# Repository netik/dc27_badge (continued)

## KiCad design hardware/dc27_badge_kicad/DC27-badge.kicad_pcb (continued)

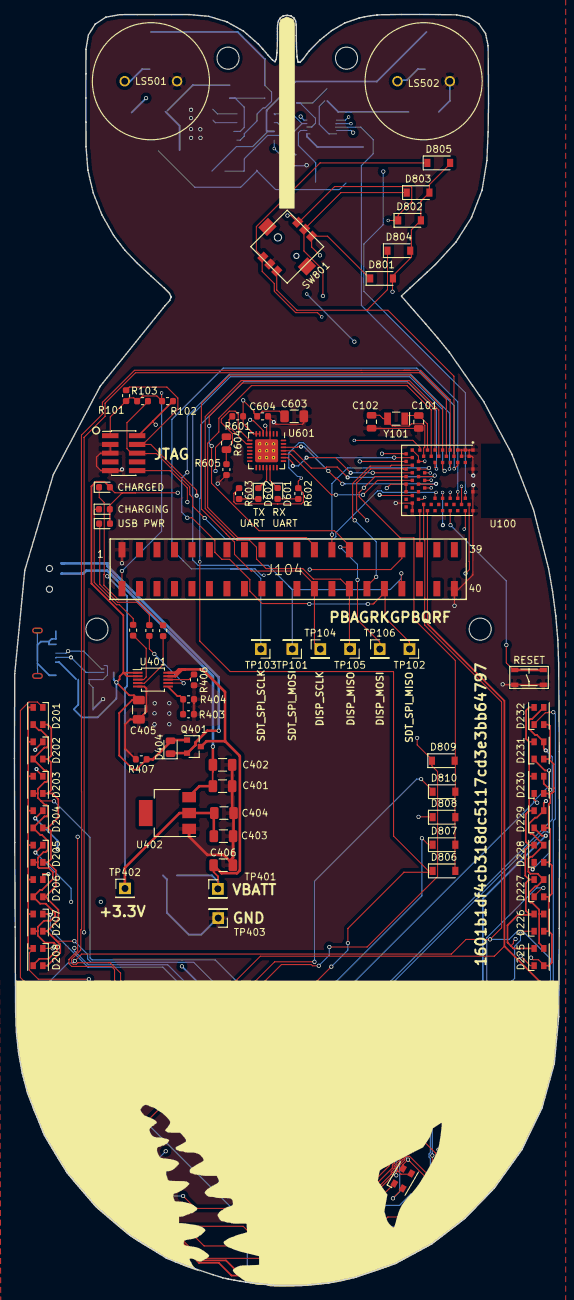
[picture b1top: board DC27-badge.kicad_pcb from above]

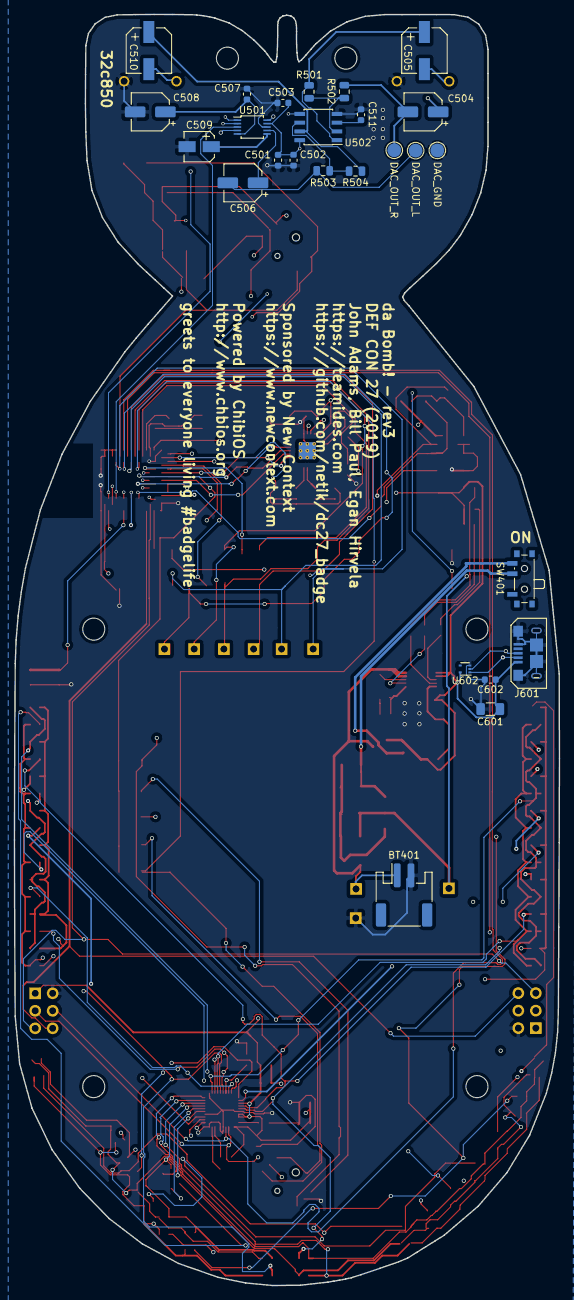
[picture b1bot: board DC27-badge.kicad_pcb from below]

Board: 4 copper layers, 79.1 x 184.5 mm, 141 parts (26 on the bottom side), 98 nets.

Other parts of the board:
D806, D807, D808, D809, D810: BAT42W-V; D_SOD-123
H701: Bomb Face; bombface-moved

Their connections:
~B_DOWN: D810.1; also elsewhere on the board
~B_LEFT: D807.1; also elsewhere on the board
~B_RIGHT: D809.1; also elsewhere on the board
~B_SELECT: D808.1; also elsewhere on the board
~B_UP: D806.1; also elsewhere on the board
~JOYPAD_INTR: D806.2, D807.2, D808.2, D809.2, D810.2; also elsewhere on the board

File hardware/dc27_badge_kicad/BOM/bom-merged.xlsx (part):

new
DESIGNATOR | VALUE | PACKAGE | MPN | XORIGIN | YORIGIN | WIDTH | HEIGHT
BT401 | Battery | Connector_JST:JST_PH_S2B-PH-SM4-TB_1x02-1MP_P2.00mm_Horizontal | S2B-PH-SM4-TB(LF)(SN) | 85.75 | -152.9 | 0 | 0
C102 | 12pF | Capacitor_SMD:C_0805_2012Metric | CC0805JRNPO9BN120 | 114.2 | -99.8 | 0 | 0
C101 | 12pF | Capacitor_SMD:C_0805_2012Metric | CC0805JRNPO9BN120 | 117.66200000000001 | -99.4 | 0 | 0
C301 | 1uF | Capacitor_SMD:C_0603_1608Metric | MF-CAP-0603-1uF | 108.2 | -194.2 | 0 | 0
C303 | 1uF | Capacitor_SMD:C_0603_1608Metric | MF-CAP-0603-1uF | 111 | -190.8 | 0 | 0
C305 | 1uF | Capacitor_SMD:C_0603_1608Metric | MF-CAP-0603-1uF | 102.57 | -197.01 | 0 | 0
C309 | 1uF | Capacitor_SMD:C_0603_1608Metric | MF-CAP-0603-1uF | 109.6 | -202.6 | 0 | 0
C302 | 0.1uF | Capacitor_SMD:C_0603_1608Metric | MF-CAP-0603-0.1uF | 108.21250000000001 | -191.6 | 0 | 0
C304 | 0.1uF | Capacitor_SMD:C_0603_1608Metric | MF-CAP-0603-0.1uF | 111 | -187.6 | 0 | 0
C306 | 0.1uF | Capacitor_SMD:C_0603_1608Metric | MF-CAP-0603-0.1uF | 102.57 | -200.06 | 0 | 0
C501 | 0.1uF | Capacitor_SMD:C_0603_1608Metric | MF-CAP-0603-0.1uF | 106.45 | -60.222499999999997 | 0 | 0
C507 | 0.1uF | Capacitor_SMD:C_0603_1608Metric | MF-CAP-0603-0.1uF | 110.96 | -50.612499999999997 | 0 | 0
C503 | 0.1uF | Capacitor_SMD:C_0603_1608Metric | MF-CAP-0603-0.1uF | 105.7375 | -51.9 | 0 | 0
C602 | 0.1uF | Capacitor_SMD:C_0603_1608Metric | MF-CAP-0603-0.1uF | 92.68 | -80.08 | 0 | 0
C604 | 0.1uF | Capacitor_SMD:C_0603_1608Metric | MF-CAP-0603-0.1uF | 101.61199999999999 | -97.4 | 0 | 0
C401 | 10uF | Capacitor_SMD:C_1206_3216Metric | MF-CAP-1206-10uF | 93.4 | -137.1 | 0 | 0
C402 | 10uF | Capacitor_SMD:C_1206_3216Metric | MF-CAP-1206-10uF | 93.4 | -134 | 0 | 0
C403 | 10uF | Capacitor_SMD:C_1206_3216Metric | MF-CAP-1206-10uF | 93.53 | -144.36000000000001 | 0 | 0
C404 | 10uF | Capacitor_SMD:C_1206_3216Metric | MF-CAP-1206-10uF | 93.6 | -141 | 0 | 0
C405 | 10uF | Capacitor_SMD:C_1206_3216Metric | MF-CAP-1206-10uF | 87.8 | -134.4 | 0 | 0
C601 | 10uF | Capacitor_SMD:C_1206_3216Metric | MF-CAP-1206-10uF | 77.12 | -126.16 | 0 | 0
C603 | 10uF | Capacitor_SMD:C_1206_3216Metric | MF-CAP-1206-10uF | 106.2 | -97.4 | 0 | 0
C406 | 1uF | Capacitor_SMD:C_1206_3216Metric | MF-CAP-0603-1uF | 93.657499999999999 | -147.94 | 0 | 0
C407 | 1uF | Capacitor_SMD:C_0603_1608Metric | MF-CAP-0603-1uF | 85.62 | -155.49 | 0 | 0
C408 | 0.47uF | Capacitor_SMD:C_0603_1608Metric | C0603C474Z4VACTU | 93.222499999999997 | -155.31 | 0 | 0
C502 | 1uF | Capacitor_SMD:C_0603_1608Metric | MF-CAP-0603-1uF | 104.2 | -60.212499999999999 | 0 | 0
C504 | 3.3uF | Capacitor_SMD:C_0603_1608Metric | UZP1E3R3MCL1GB | 96.78 | -55.14 | 0 | 0
C506 | 3.3uF | Capacitor_SMD:C_0603_1608Metric | UZP1E3R3MCL1GB | 101.53749999999999 | -59.4 | 0 | 0
C508 | 3.3uF | Capacitor_SMD:C_0603_1608Metric | UZP1E3R3MCL1GB | 114.05 | -55.22 | 0 | 0
C505 | 100uF | Capacitor_SMD:C_0603_1608Metric | MF-CAP-6.3MM-100uF | 118.37 | -66.28 | 0 | 0
C510 | 100uF | Capacitor_SMD:C_0603_1608Metric | MF-CAP-6.3MM-100uF | 125.99 | -66.19 | 0 | 0
C509 | 10uF | Capacitor_SMD:C_0603_1608Metric | MF-CAP-4MM-10uF | 110.44752 | -61.01 | 0 | 0
C511 | 1uF Ceramic | Capacitor_SMD:C_0603_1608Metric | MF-CAP-0603-1uF | 94.4 | -53.612499999999997 | 0 | 0
D217 | LED_ARGB | LED_SMD:LED_Cree-PLCC4_3.2x2.8mm_CCW | MF-LED-3228-RGB | 108 | -220.9 | 0 | 0
D218 | LED_ARGB | LED_SMD:LED_Cree-PLCC4_3.2x2.8mm_CCW | MF-LED-3228-RGB | 113.2 | -219.8 | 0 | 0
D219 | LED_ARGB | LED_SMD:LED_Cree-PLCC4_3.2x2.8mm_CCW | MF-LED-3228-RGB | 117.4 | -218 | 0 | 0
D220 | LED_ARGB | LED_SMD:LED_Cree-PLCC4_3.2x2.8mm_CCW | MF-LED-3228-RGB | 121.3 | -216.3 | 0 | 0
D221 | LED_ARGB | LED_SMD:LED_Cree-PLCC4_3.2x2.8mm_CCW | MF-LED-3228-RGB | 125.2 | -213.4 | 0 | 0
D222 | LED_ARGB | LED_SMD:LED_Cree-PLCC4_3.2x2.8mm_CCW | MF-LED-3228-RGB | 129 | -211.2 | 0 | 0
D223 | LED_ARGB | LED_SMD:LED_Cree-PLCC4_3.2x2.8mm_CCW | MF-LED-3228-RGB | 132.69999999999999 | -207.5 | 0 | 0
D224 | LED_ARGB | LED_SMD:LED_Cree-PLCC4_3.2x2.8mm_CCW | MF-LED-3228-RGB | 140.19999999999999 | -194.57400000000001 | 0 | 0
D225 | LED_ARGB | LED_SMD:LED_Cree-PLCC4_3.2x2.8mm_CCW | MF-LED-3228-RGB | 141.74 | -175.91 | 0 | 0
D226 | LED_ARGB | LED_SMD:LED_Cree-PLCC4_3.2x2.8mm_CCW | MF-LED-3228-RGB | 141.74 | -170.91 | 0 | 0
D227 | LED_ARGB | LED_SMD:LED_Cree-PLCC4_3.2x2.8mm_CCW | MF-LED-3228-RGB | 141.74 | -165.91 | 0 | 0
D228 | LED_ARGB | LED_SMD:LED_Cree-PLCC4_3.2x2.8mm_CCW | MF-LED-3228-RGB | 141.74 | -160.91 | 0 | 0
D229 | LED_ARGB | LED_SMD:LED_Cree-PLCC4_3.2x2.8mm_CCW | MF-LED-3228-RGB | 141.74 | -155.91 | 0 | 0
D230 | LED_ARGB | LED_SMD:LED_Cree-PLCC4_3.2x2.8mm_CCW | MF-LED-3228-RGB | 141.74 | -150.91 | 0 | 0
D231 | LED_ARGB | LED_SMD:LED_Cree-PLCC4_3.2x2.8mm_CCW | MF-LED-3228-RGB | 141.74 | -145.91 | 0 | 0
D232 | LED_ARGB | LED_SMD:LED_Cree-PLCC4_3.2x2.8mm_CCW | MF-LED-3228-RGB | 141.74 | -140.91 | 0 | 0
D201 | LED_ARGB | LED_SMD:LED_Cree-PLCC4_3.2x2.8mm_CCW | MF-LED-3228-RGB | 69.010000000000005 | -140.91 | 0 | 0
D202 | LED_ARGB | LED_SMD:LED_Cree-PLCC4_3.2x2.8mm_CCW | MF-LED-3228-RGB | 69.010000000000005 | -145.91 | 0 | 0
D203 | LED_ARGB | LED_SMD:LED_Cree-PLCC4_3.2x2.8mm_CCW | MF-LED-3228-RGB | 69.010000000000005 | -150.91 | 0 | 0
D204 | LED_ARGB | LED_SMD:LED_Cree-PLCC4_3.2x2.8mm_CCW | MF-LED-3228-RGB | 69.010000000000005 | -155.91 | 0 | 0
D205 | LED_ARGB | LED_SMD:LED_Cree-PLCC4_3.2x2.8mm_CCW | MF-LED-3228-RGB | 69.010000000000005 | -160.91 | 0 | 0
D206 | LED_ARGB | LED_SMD:LED_Cree-PLCC4_3.2x2.8mm_CCW | MF-LED-3228-RGB | 69.010000000000005 | -165.91 | 0 | 0
D207 | LED_ARGB | LED_SMD:LED_Cree-PLCC4_3.2x2.8mm_CCW | MF-LED-3228-RGB | 69.010000000000005 | -170.91 | 0 | 0
D208 | LED_ARGB | LED_SMD:LED_Cree-PLCC4_3.2x2.8mm_CCW | MF-LED-3228-RGB | 69.010000000000005 | -175.91 | 0 | 0
D209 | LED_ARGB | LED_SMD:LED_Cree-PLCC4_3.2x2.8mm_CCW | MF-LED-3228-RGB | 69.900300000000001 | -194.57400000000001 | 0 | 0
D210 | LED_ARGB | LED_SMD:LED_Cree-PLCC4_3.2x2.8mm_CCW | MF-LED-3228-RGB | 76.900000000000006 | -207.5 | 0 | 0
D211 | LED_ARGB | LED_SMD:LED_Cree-PLCC4_3.2x2.8mm_CCW | MF-LED-3228-RGB | 80.599999999999994 | -211.2 | 0 | 0
D212 | LED_ARGB | LED_SMD:LED_Cree-PLCC4_3.2x2.8mm_CCW | MF-LED-3228-RGB | 84.3 | -213.4 | 0 | 0
D213 | LED_ARGB | LED_SMD:LED_Cree-PLCC4_3.2x2.8mm_CCW | MF-LED-3228-RGB | 88.1 | -216.3 | 0 | 0
D214 | LED_ARGB | LED_SMD:LED_Cree-PLCC4_3.2x2.8mm_CCW | MF-LED-3228-RGB | 92.4 | -218 | 0 | 0
D215 | LED_ARGB | LED_SMD:LED_Cree-PLCC4_3.2x2.8mm_CCW | MF-LED-3228-RGB | 96.7 | -219.8 | 0 | 0
D216 | LED_ARGB | LED_SMD:LED_Cree-PLCC4_3.2x2.8mm_CCW | MF-LED-3228-RGB | 102.7 | -220.9 | 0 | 0
D401 | CHG | Diode_SMD:D_0603_1608Metric | MF-LED-0603-RED | 81.400000000000006 | -112.4 | 0 | 0
D402 | DONE | Diode_SMD:D_0603_1608Metric | MF-LED-0603-GREEN | 81.400000000000006 | -117.9 | 0 | 0
D601 | TX LED | Diode_SMD:D_0603_1608Metric | MF-LED-0603-RED | 103.8 | -108.6 | 0 | 0
D602 | RX LED | Diode_SMD:D_0603_1608Metric | MF-LED-0603-GREEN | 101 | -108.61199999999999 | 0 | 0
J101 | Conn_ARM_JTAG_SWD_10 | Connector_PinHeader_1.27mm:PinHeader_2x05_P1.27mm_Vertical_SMD | 20021121-00010C4LF | 81.45 | -102.75 | 0 | 0
J102 | ShittyAddOnL | Connector_PinSocket_2.54mm:PinSocket_2x02_P2.54mm_Vertical_SMD | SSM-102-L-DV | 139 | -184.3 | 0 | 0
J103 | ShittyAddOnR | Connector_PinSocket_2.54mm:PinSocket_2x02_P2.54mm_Vertical_SMD | SSM-102-L-DV | 71.3 | -183.8 | 0 | 0
J104 | Conn_02x20_Odd_Even | samtec:SAMTEC-SSM-120-X-DV | SSM-120-L-DV-K-TR | 105.33 | -126.6 | 0 | 0
J601 | USB_MICRO_RIGHT | MF_Connectors:MF_Connectors-MICROUSB-RIGHT | MF-CON-MICROUSB-RIGHT | 70.33 | -131.80000000000001 | 0 | 0
R101 | 10K | Resistor_SMD:R_0603_1608Metric | MF-RES-0603-10K | 81.8 | -94.4 | 0 | 0
R102 | 10K | Resistor_SMD:R_0603_1608Metric | MF-RES-0603-10K | 87.8125 | -95.2 | 0 | 0
R103 | 10K | Resistor_SMD:R_0603_1608Metric | MF-RES-0603-10K | 84.1875 | -95.2 | 0 | 0
R302 | 20K | Resistor_SMD:R_0603_1608Metric | MF-RES-0805-20K | 108.5125 | -200 | 0 | 0
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
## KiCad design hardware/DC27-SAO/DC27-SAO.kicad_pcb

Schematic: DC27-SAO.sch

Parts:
C1, C4: 2.2uF; C_0603_1608Metric
C2, C3, C5: 1uF; C_0603_1608Metric
C6: 22nF; C_0603_1608Metric
D1, D2, D3, D4, D5, D6, D7, D8, D9: LED; LED_0603_1608Metric
DS1: ER-OLED0.84-1; PinHeader_1x14_P1.00mm_Horizontal
J1: ISP; PinHeader_2x03_P1.00mm_Vertical
JP1: SCL SOURCE; SolderJumper-3_P1.3mm_Bridged12_Pad1.0x1.5mm
JP2: SDA SOURCE; SolderJumper-3_P1.3mm_Bridged12_Pad1.0x1.5mm
R1, R2, R3, R4, R5, R6, R7, R8, R9: 70; R_0603_1608Metric
R10: 1k; R_0603_1608Metric
R11, R12: 2k; R_0603_1608Metric
R13: 820k; R_0603_1608Metric
SW1: UP; MF_Switches-TACT4.2MM
SW2: SEL; MF_Switches-TACT4.2MM
SW3: DN; MF_Switches-TACT4.2MM
U1: ATtiny2313-20PU; SOIC-20W_7.5x12.8mm_P1.27mm
X1: Badgelife_shitty_connector; Badgelife-SAO

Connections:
DISP_SCK: DS1.10, JP1.2, R12.2
DISP_SDA: DS1.11, JP2.2, R11.2
GND: C1.2, C4.2, C5.2, C6.2, D1.1, D2.1, D3.1, D4.1, D5.1, D6.1, D7.1, D8.1, D9.1, DS1.7, J1.6, R13.2, U1.10 (GND), X1.2
LED_B: R3.2, R6.2, R9.2, U1.6 (PD2)
LED_G: R2.2, R5.2, R8.2, U1.3 (PD1)
LED_R: R1.2, R4.2, R7.2, U1.2 (PD0)
unnamed: C2.1, DS1.3
unnamed: C2.2, DS1.4
unnamed: C3.1, DS1.1
unnamed: C3.2, DS1.2
unnamed: C4.1, DS1.13
unnamed: C6.1, DS1.6
unnamed: D1.2, R1.1
unnamed: D2.2, R2.1
unnamed: D3.2, R3.1
unnamed: D4.2, R4.1
unnamed: D5.2, R5.1
unnamed: D6.2, R6.1
unnamed: D7.2, R7.1
unnamed: D8.2, R8.1
unnamed: D9.2, R9.1
unnamed: DS1.12, R13.1
PB0: J1.4, JP2.1, U1.12 (PB0)
PB1: J1.1, U1.13 (PB1)
SAO_SCK: JP1.3, X1.3
SAO_SDA: JP2.3, X1.4
SCK: J1.3, JP1.1, U1.14 (PB2)
VCC: C1.1, C5.1, DS1.5, DS1.8, DS1.14, J1.2, R10.1, R11.1, R12.1, U1.20 (VCC), X1.1
~RESET: DS1.9, J1.5, R10.2, U1.1 (PA2/~RESET)

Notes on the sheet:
These jumpers control if our MCU or the SAO’s MCPU is in charge of the screen.
Connector: ER-CON14HT-1 maybe?
pogo pins ISP?
Note to self: There’s about ten pins here, we could drive all the LED elements individually.
20ma RED, 2V Fwd 3.3v VCC
10ma GREEN, 2.1V Fwd 3.3v VCC
10ma BLUE, 2.1V Fwd 3.3v VCC

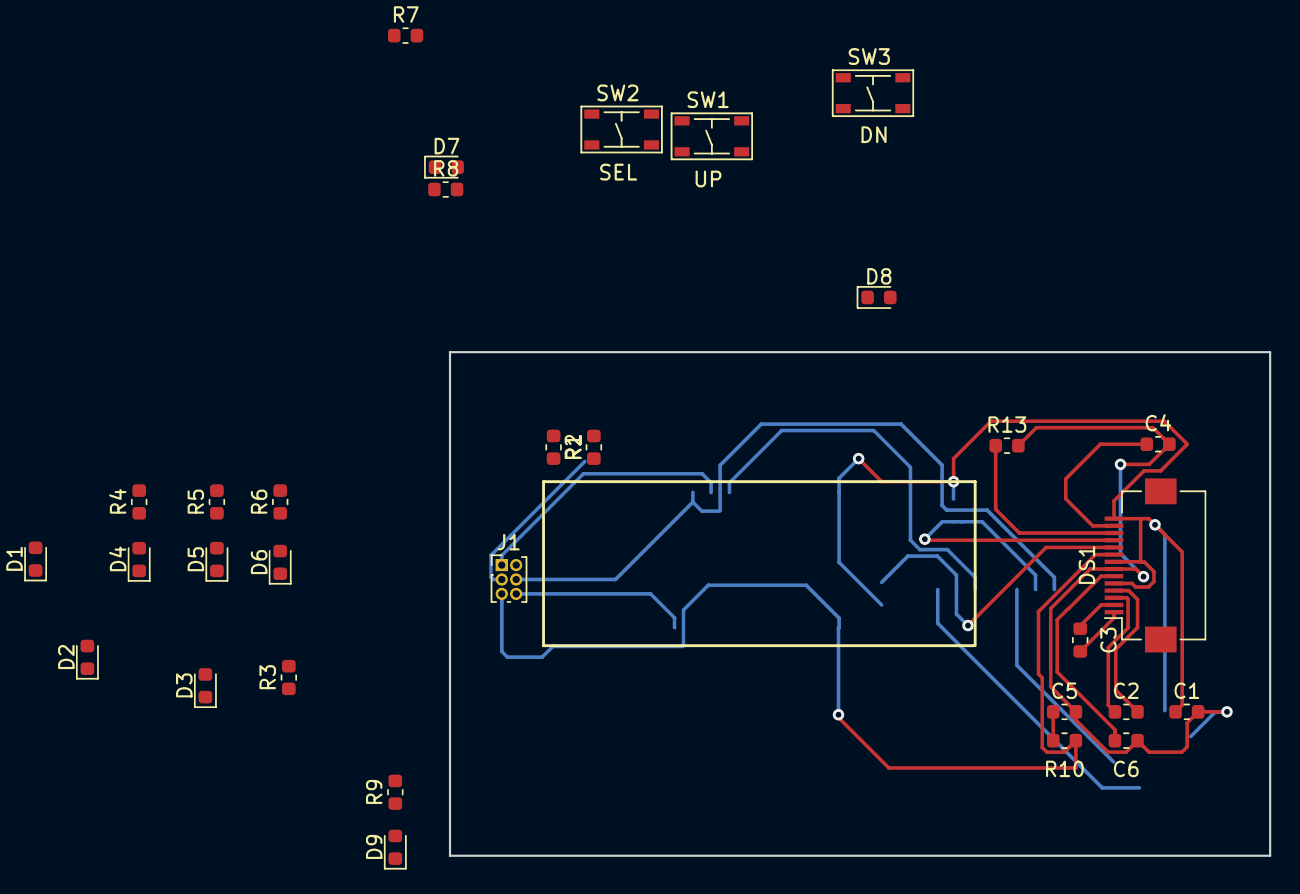
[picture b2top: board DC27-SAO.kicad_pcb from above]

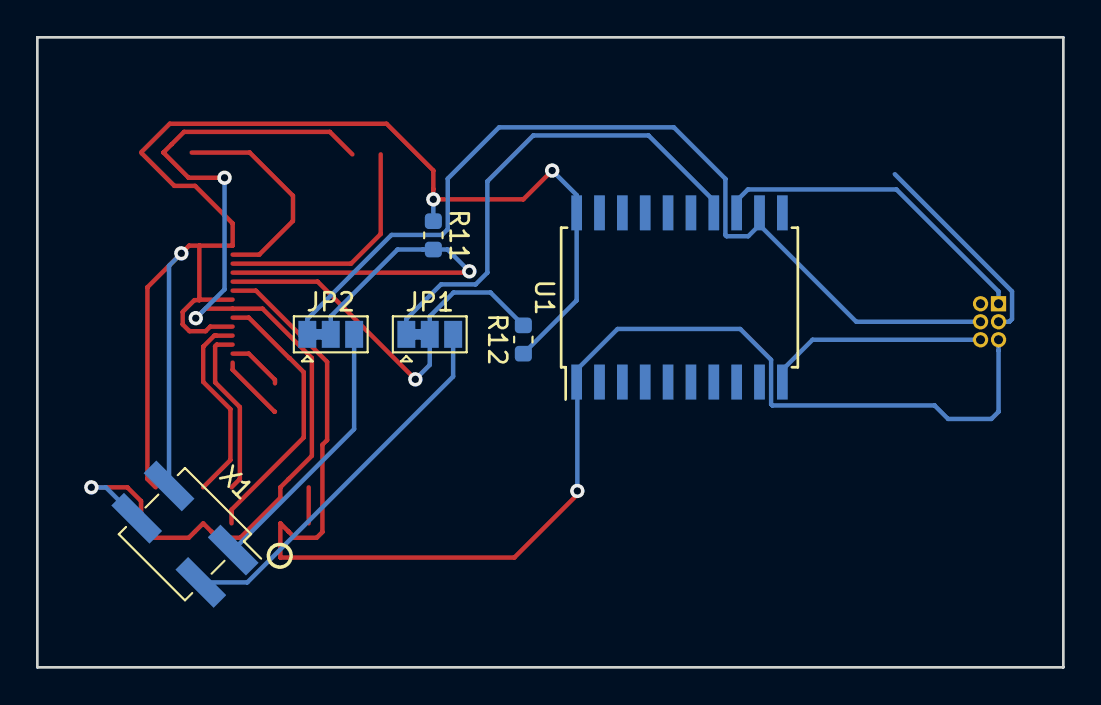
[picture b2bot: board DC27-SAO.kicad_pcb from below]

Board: 2 copper layers, 57.0 x 35.0 mm, 37 parts (6 on the bottom side), 29 nets.

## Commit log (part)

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2019-06-05 if ffmpeg fails to translate a file, have it bomb out so we don't write 8-byte files with only the header to the sd card.
2019-06-07 Remember to always destroy the list UI on exit
2019-06-07 add some new media
2019-06-07 hide the unlock app and fix an edge case in launcher
2019-06-08 Fix a small I2C stability issue
    When compiled without LTO, sometimes reads will return success even
    if there's no device present on the I2C bus (such as with a Nordic
    DK board with no LEDs). It looks like we need to force a few write
    drains to the I2C registers in the interrupt handler to make sure
    the driver and hardware stay in sync.
2019-06-08 Fix keyASelect handling in launcher
    For some reason this button wasn't being sensed in the launcher.
2019-06-08 Avoid overwriting names with "<none>" all the time.
2019-06-09 Add 1950s NY Civil Defense drill video
2019-06-09 Add one more video
2019-06-09 Fix typo
2019-06-10 fix startup order so factory reset tone still works
2019-06-11 seriously clean up the drawing routines so that the world map is smooth.
2019-06-11 give a few more px to app-launcher so ble address displays correctly
2019-06-12 update credits.tif with ciph3r's image
2019-06-12 Protect the gamma correction table with #ifdef USE_GAMMA/#endif
2019-06-13 Allow .gif images to be used for icons
    The sdcard Makefile now generates both .rgb and .gif images from .tif
    icon files. The .gif versions have transparent backgrounds, and it
    is now possible to use putImageFile() for both .rgb and .gif images.
    This spruces up the launcher quite a bit.
    Also, the rickrolling e-mail app has now been turned into a
    rickrolling Bitcoin miner app (with nice shiny Bitcoin icon), which
2019-06-13 add new codes
2019-06-13 add led effects to unlock
2019-06-14 Try to upgrade the link to 2MBPS when we're the central.
2019-06-14 Add a radio remote unlocker app
    A special unlock flag called UL_BLACKBADGE has been added. This
    attribute can not be unlocked by the app-unlock puzzle app. It either
    has to be set as a default bit in the userconfig at compile time,
    or it has to be unlocked by phone or someone else with a black
    badge.
    Two new orchard app flags have been added: APP_FLAG_UNLOCK and
2019-06-14 Make sure unlock logic is correct
2019-06-15 32 bytes is a little too small for the peer thread stack.
    Make it 128 instead, just for paranoia's sake.
2019-06-15 Add a short delay here too
2019-06-15 attempt to make zmachine go with sdget()
2019-06-15 start to port over file code
2019-06-16 Fix a memory leak.
    I think this bug has been in this code since it was written. When
    releasing cache, remember to free the final node.
2019-06-16 Add the jzip Z-Machine to the master branch
    You can now run Zork from the shell using the xyzzy command. This is
    based on the JZip Z-Machine written by John Holder, which can be found
    at: http://jzip.sourceforge.net/
    This was later ported to the Arduino by DanTheGeek as the A2Z Machine,
    which can be found here: https://github.com/ZContent/A2Z_Machine
    Much of the code has been reverted back to its original JZip 2.1 form.
2019-06-16 Argh, turn LTO back on
2019-06-16 Add _stat and _fstat syscall handlers
    Also, fix error handling for open/close/read/write.
2019-06-17 add howto photo image
2019-06-17 fix missing unlock code
2019-06-17 remove very large zmachine games
2019-06-17 clean up led menu; make led unlocks work
2019-06-17 Fix filename collision
    I failed to notice there was already an unlock.tif image that
    goes with the app-unlock.c app. This gets overwritten by the
    unlock.jpg image during SD card creation (both get converted to
    unlock.rgb).
    To fix the conflict, the remote radio unlock app now uses
    runlock.jpg/rgb instead.
2019-06-17 ships minor structure cleanup
2019-06-19 add note to zmachine startup
2019-06-19 Add Sex Bomb by Tom Jones
2019-06-19 Have the getbom script run jsonpp for cleanups after download.
    Check in these downloads so someone else can have them later.
2019-06-20 allow apps to have auto init turned on and not be hidden in the launcher
2019-06-20 disable enemy discovery
2019-06-21 Undo gratuitous whitespace changes
    Also remove BLE_GAP_VERBOSE left at the top of ble_gap_lld.c.
2019-06-22 add a double-buffered dual temp display to the badge screen, have it update every five seconds.
2019-06-23 Reduce temperature redraws
    Only redraw the temperature on the home screen if the temperature
    actually changes.
2019-06-25 check to see if libusb is in /opt/local, and if so, use it..
2019-06-25 move to using Makefile to generate these, add program for card gen...
2019-06-25 Revert accidental change to cmd-radio.c
2019-06-25 Add "radio active" warning image
    I may use this for the BLE geiger counter app
2019-06-26 add puzzle mode unlock... make user config a bit more robust by automatically detecting when the structure gets extended, and reiniting it... orchard hasn't been taught to expose the puzzle apps yet..
2019-06-27 make this importable so you can work w/ the shuffled deck
2019-06-27 Upgrade to SoftDevice S140 version 7.0.0
2019-06-27 forgot to mark this as a puzzle...
2019-06-29 Switch the pix buff over from dynamic to static so that we can switch between the world map and the local map, fix memory leaks
2019-06-30 add sprite system
2019-06-30 Use the LED array in the geiger app
    We attempt to measure the intensity of received advertisements
    by seeing how fast the arrive, using a hardware timer, and jigger
    the LED array to display it.
2019-07-02 Make the ledDraw() function a led library routine
    Both the geiger counter and music player app use it, so why not
    make it common code.
2019-07-03 add party invite
2019-07-03 Fix a bug with the updater
    I added code to disable the SPI buses before launching the updater
    program. I think in some cases, with compiler optimization, the
    SPI bus may be disabled before we're really finished reading from it.
    Inserting an instruction barrier between the f_close() and spiStop()
    calls should prevent this from happening (either due to compiler
    re-ordering or CPU re-ordering of operations).
2019-07-03 update c files to match new icons
2019-07-03 fix party code
2019-07-05 Get rid of references to chprintf()
    Use printf() instead.
2019-07-07 Add initial combat position table
    This table defines the initial positions when combat begins
    on a grid rectangle.
2019-07-08 Add handshaking game state, which happens just after our l2cap connection.
    Fix math on land collisions and make land collision work again in
    WORLD_MAP.
    Fix interaction between app-notify and app-battle so that
    the battle app gets current_enemy data on start. Fix this so it
    works if we start in sea battle or outside of it.
2019-07-08 remove my ble gap debugging statement
2019-07-09 Fix some documentation nits
2019-07-10 Copy the config into a 'live' player struct on battle start.
    Consoliate player and enemy code in a lot of places so that we're not
    having to make special snowflake code for the player. Eeveryone's an
    instance of ENEMY now. I hate you. #punk
    Advertise the player's ship type along with their rank so we have it
    at combat start (and potentially, later, could do custom world_map
    icons w/o protocol chnages)
2019-07-11 Everything up to the COMBAT screen is now working.
    We're not drawing ships yet on that screen (will do tomorrow) but our
    clocks work, the VS ship selection is functional, and moving to the
    correct map is working. The attacker is in charge of what map we land
    on to prevent players being split between maps and proper maps are
    being drawn.
    Initial combat screen is drawn correctly as well. Nearly there.
2019-07-11 Fix compiler warnings about type-punning.
2019-07-12 Add a rand uint16 function.
    Assign random id #'s to created entities for bullet tracking.
2019-07-13 whitespace cleanup enemy.c/.h
2019-07-14 Fix a uGFX event processing issue
    We only preserve one uGFX event when the uGFX orchard callback is called.
    But there are some instances where two events may be generated in rapid
    succession by the gtimer thread, and it has higher priority that the
    app thread. This means that sometimes an event can be delivered, then
    overwritten with another event before the app gets a chance to process
    it.
2019-07-14 add prototype
2019-07-15 Add an alternate USB provisioning script
    This script is similar to the other, except it obtains the
    Nordic nRF52840 device ID and uses that as the serial number
    string. Each chip has a unique ID, which saves us from having
    to invent a new one.
2019-07-16 Only respond to mouse-down touch events
    We were responding to both press and release events before. We
    need to ignore the "mouse up" events.
2019-07-16 handle null errors when dealing with bullets
2019-07-17 Clear the screen on exit
    This seems to get rid of some artifacts that are sometimes
    visible right before launching an app.
2019-07-17 update sprite lib with new code from devon
2019-07-18 cleanup ispholders on combat exit
2019-07-18 fix bg color merge
2019-07-18 Fix stale comment
2019-07-18 Move enemy definition to enemy.h
    Start in on support for some more specials
    Modify VS packets to send user's unlock status as well as ship status
    Modify all L2Cap packets to actually be bounded by 4-byte chunks. Fix padding.
2019-07-19 Add variable bullet size per ship class and fix energy reporting on special usage.
2019-07-19 add sheilds
2019-07-19 speed fixes and updates
2019-07-19 fix typo in active setting for slab alloc
2019-07-20 Fix crash on exit in battle game
    We need to avoid drawing sprites after they've been destroyed.
2019-07-21 memory leak and bug fixes in ides_sprite.c
2019-07-21 Add buffering to the video player
    Testing with the production video card showed that video playback was
    unacceptably slow. Rewriting the video card with my FreeBSD machine
    yielded much better behavior with the same SD card hardware. I suspect
    that the data on the master image was written in a less linear fashion
    (meaning that files were not always written in nice successive streams
    of sectors on disk) which causes lots of seeking when reading back
2019-07-22 Fix a double-free bug in isp_shutdown()
    Destroying the world map also releases its memory. No need to do it
    a second time.
2019-07-22 Remember to use the peer list mutex.
2019-07-22 Update chat app to filter peers
    Only allow peers to show up in the chat list if they're badges.
    We use the peerlist mechanism for this. This is to avoid being
    flooded with non-badge BLE peers in the list (who we can't chat
    with anyway).
2019-07-22 make won/lost setttable in cmd-config
2019-07-22 When exiting a battle request, exit to the main menu.
    Otherwise, we will see a radio signal loss, which isn't really true.
2019-07-23 Fix bug in ugfxEvent handling
    The logic to prevent overlapped ugfxEvents from occurring wasn't
    quite right. Sometimes we wouldn't clear the pending status and
    uGFX events would stop. This should be fixed now.
2019-07-23 When calling ledSetPattern(), clear the LEDs if the current pattern is "off"
    When apps that frob the LEDs exit and the current LED pattern is
    "off," some LEDs may remain set until the next time the array is
    used. All those apps call ledSetPattern() on exit though, so if
    the current pattern is off, we should set all LEDs to 0 PWM.
    Closes #51
2019-07-23 remove all printf's and place them under ifdef's for debugging
2019-07-24 Fix some last minute bugs
    Make levelling up to WOPR actually work correctly.
    Correct level cap calculation
    Fix black badge config commands so that they can be enabled at
    runtime instead of at compile time.
2019-07-27 Add a Doomguy app
    This app just displays an animated Doomguy face on the screen.
    It will honor the screen rotation setting so that it displays
    correctly when the badge is hanging from your neck, like the
    LED sign app.
